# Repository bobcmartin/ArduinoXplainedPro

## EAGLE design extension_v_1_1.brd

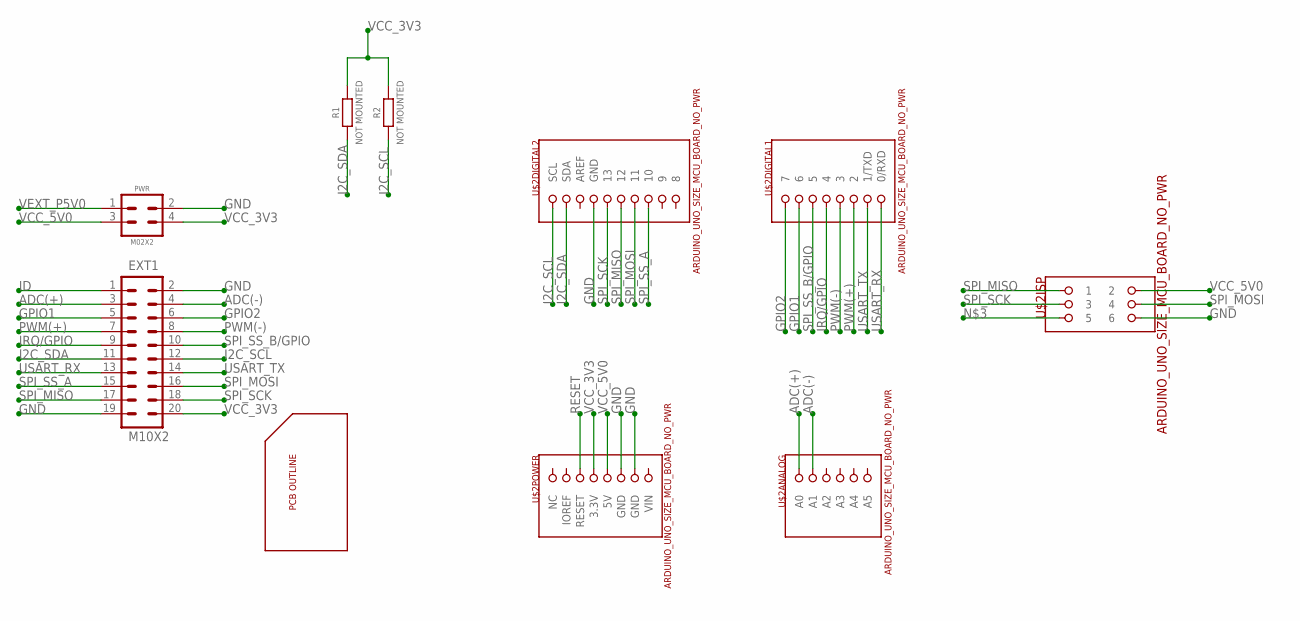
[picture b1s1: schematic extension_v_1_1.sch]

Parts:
EXT1: M10X2; 2X10
PWR: M02X2; H4X2_100_MIL
R1, R2: NOT MOUNTED; 0603
U$2: ARDUINO_UNO_SIZE_MCU_BOARD_NO_PWR; STANDARD_NO_PWR

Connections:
ADC(+): EXT1.3, U$2.9 (A0)
ADC(-): EXT1.4, U$2.11 (A1)
GND: EXT1.2, EXT1.19, PWR.2, U$2.6 (GND), U$2.7 (GND), U$2.30 (GND), U$2.ISCP6 (6)
GPIO1: EXT1.5, U$2.22 (6)
GPIO2: EXT1.6, U$2.23 (7)
I2C_SCL: EXT1.12, R2.1, U$2.60 (SCL)
I2C_SDA: EXT1.11, R1.1, U$2.50 (SDA)
ID: EXT1.1
IRQ/GPIO: EXT1.9, U$2.20 (4)
PWM(+): EXT1.7, U$2.18 (2)
PWM(-): EXT1.8, U$2.19 (3)
RESET: U$2.3 (RESET)
SPI_MISO: EXT1.17, U$2.28 (12), U$2.ICSP1 (1)
SPI_MOSI: EXT1.16, U$2.27 (11), U$2.ISCP4 (4)
SPI_SCK: EXT1.18, U$2.29 (13), U$2.ISCP3 (3)
SPI_SS_A: EXT1.15, U$2.26 (10)
SPI_SS_B/GPIO: EXT1.10, U$2.21 (5)
USART_RX: EXT1.13, U$2.16 (0/RXD)
USART_TX: EXT1.14, U$2.17 (1/TXD)
VCC_3V3: EXT1.20, PWR.4, R1.2, R2.2, U$2.4 (3.3V)
VCC_5V0: PWR.3, U$2.5 (5V), U$2.ICSP2 (2)
VEXT_P5V0: PWR.1

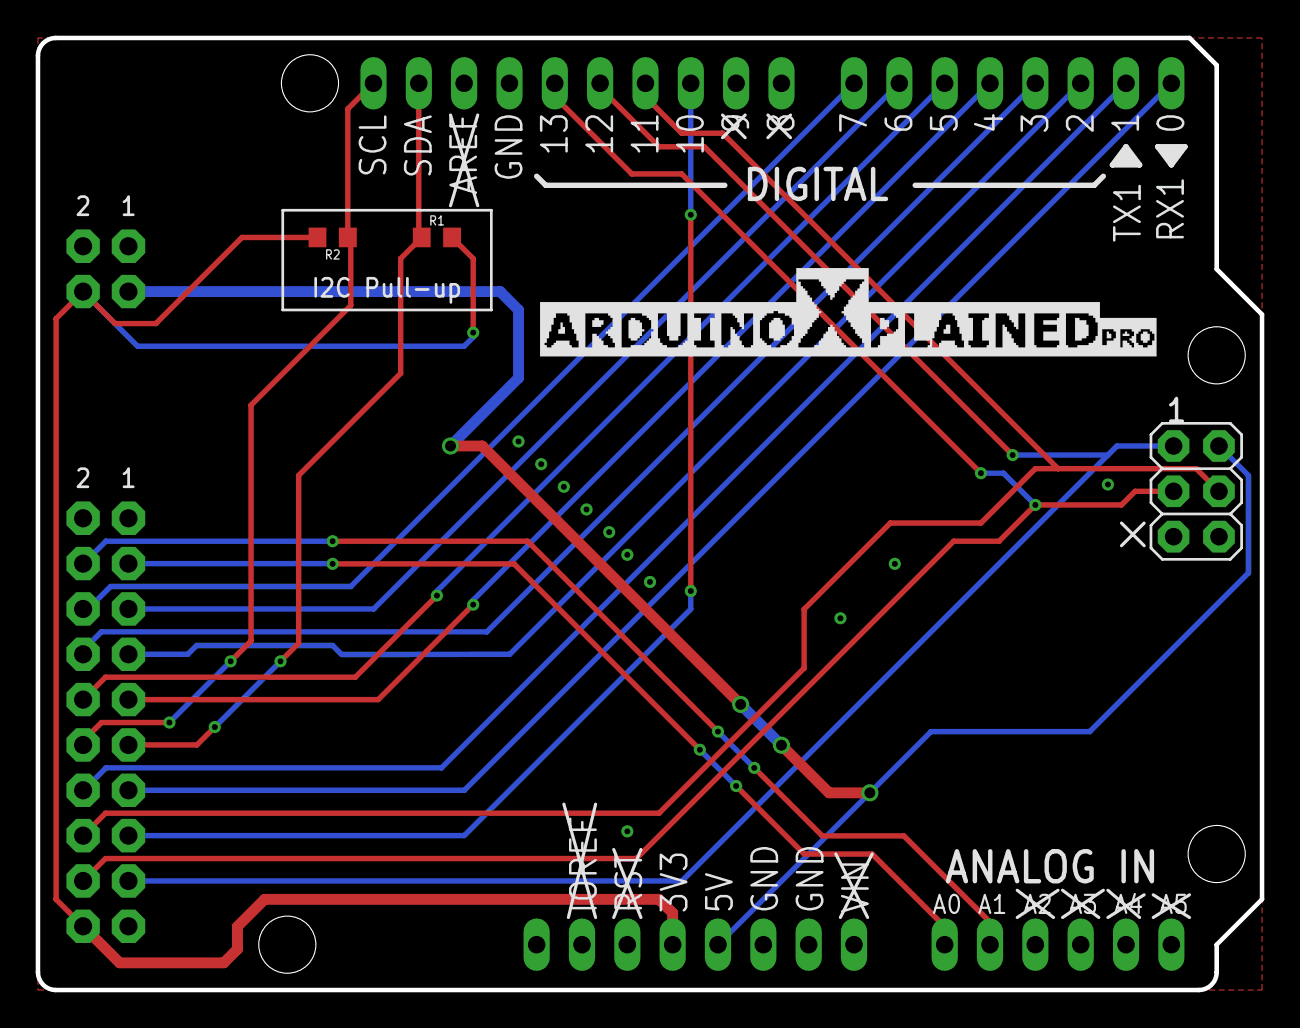
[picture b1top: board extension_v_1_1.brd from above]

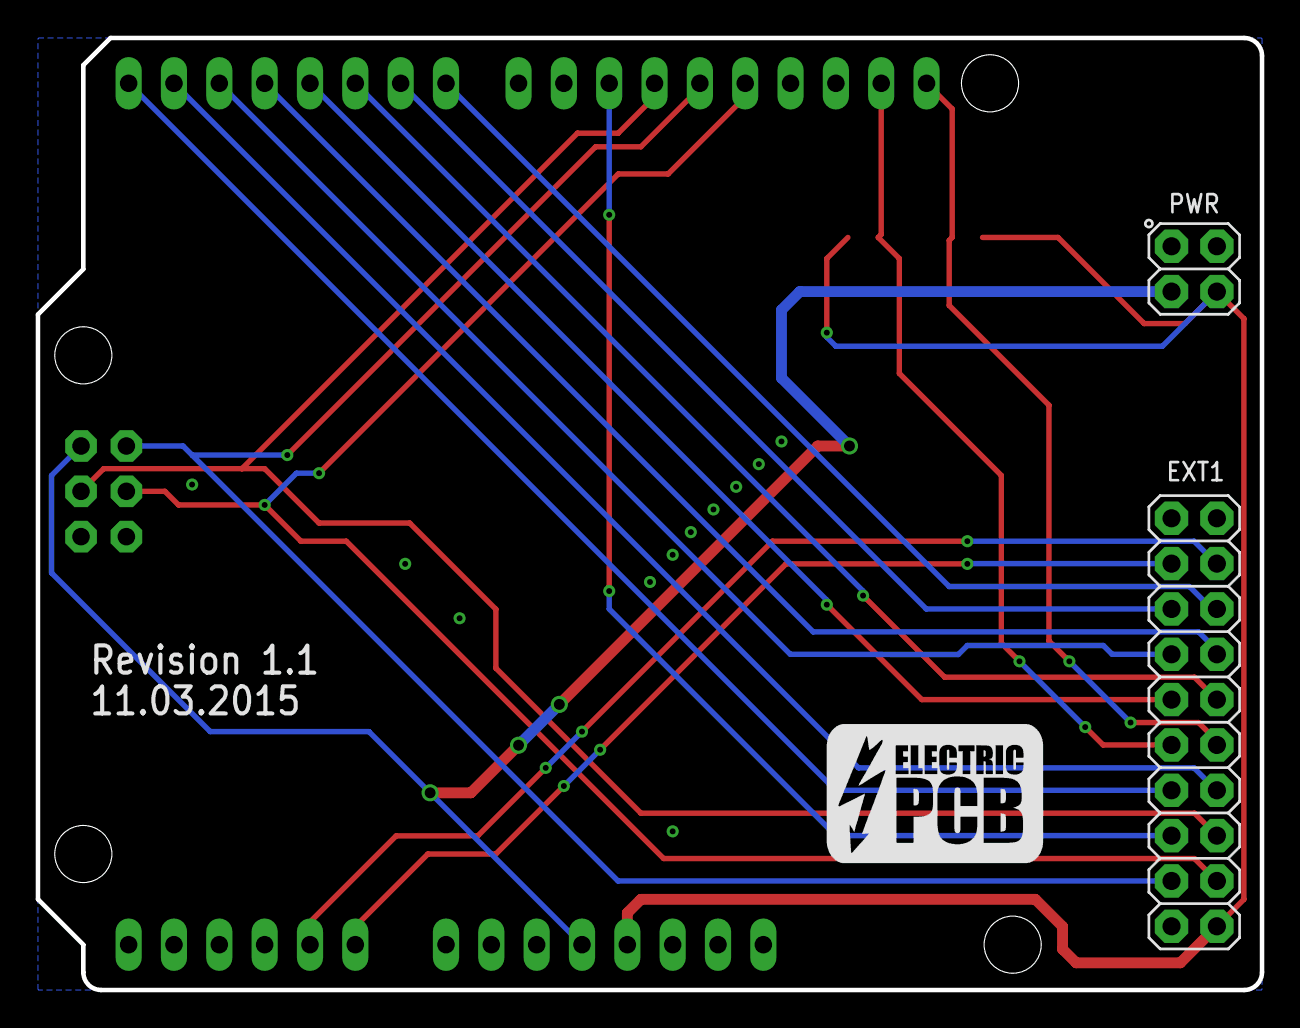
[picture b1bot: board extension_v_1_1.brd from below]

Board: 2 copper layers, 68.6 x 53.3 mm, 7 parts (3 on the bottom side), 19 nets.

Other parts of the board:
U$1: ARDUINOXPLAINEDPRO
U$3: ELECTRIC_PCB_LOGO

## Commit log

2014-01-20 Added initial .gitignore file
2014-01-20 Added board, schematc and eagle project
2014-01-20 Added gerber files for production
2014-03-12 Added production gerbers and schematic
2014-03-12 Moved to the production file folder
2015-03-11 Fixed bug where SDL and SDA pins were interchanged
2015-03-11 Added version 1.1 production files

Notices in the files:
parts and their libraries:
SparkFun: Licensing: CC v3.0 Share-Alike You are welcome to use this library for commercial purposes.
